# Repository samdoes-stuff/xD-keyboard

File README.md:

# xD-keyboard
xD keyboard is nRF52 based wireless mechanical keyboard equipped with Gateron KS-33 low profile key switches. 

# PCB 

Generated with KLEPCBGEN. Designed with both Kicad & Easyeda PRO.

# Case & Plate 

Generated with Swillkb & Keebio. Designed with Fusion 360. Chopped with Bamboo lab Studio.

Counter sink screw holes

# Bootloader & Firmware

Bootloader generated from Adafruit_nRF52_Bootloader & Firmware made with ZMK with Custom Board.
- ZMK Ultra-Low-Power Mode
- Deep sleep between keypresses
- BLE connection optimization
- Soft-off / idle timeout
- ZMK USB HID (wired mode)

#BOM 

Refer to BOM.csv

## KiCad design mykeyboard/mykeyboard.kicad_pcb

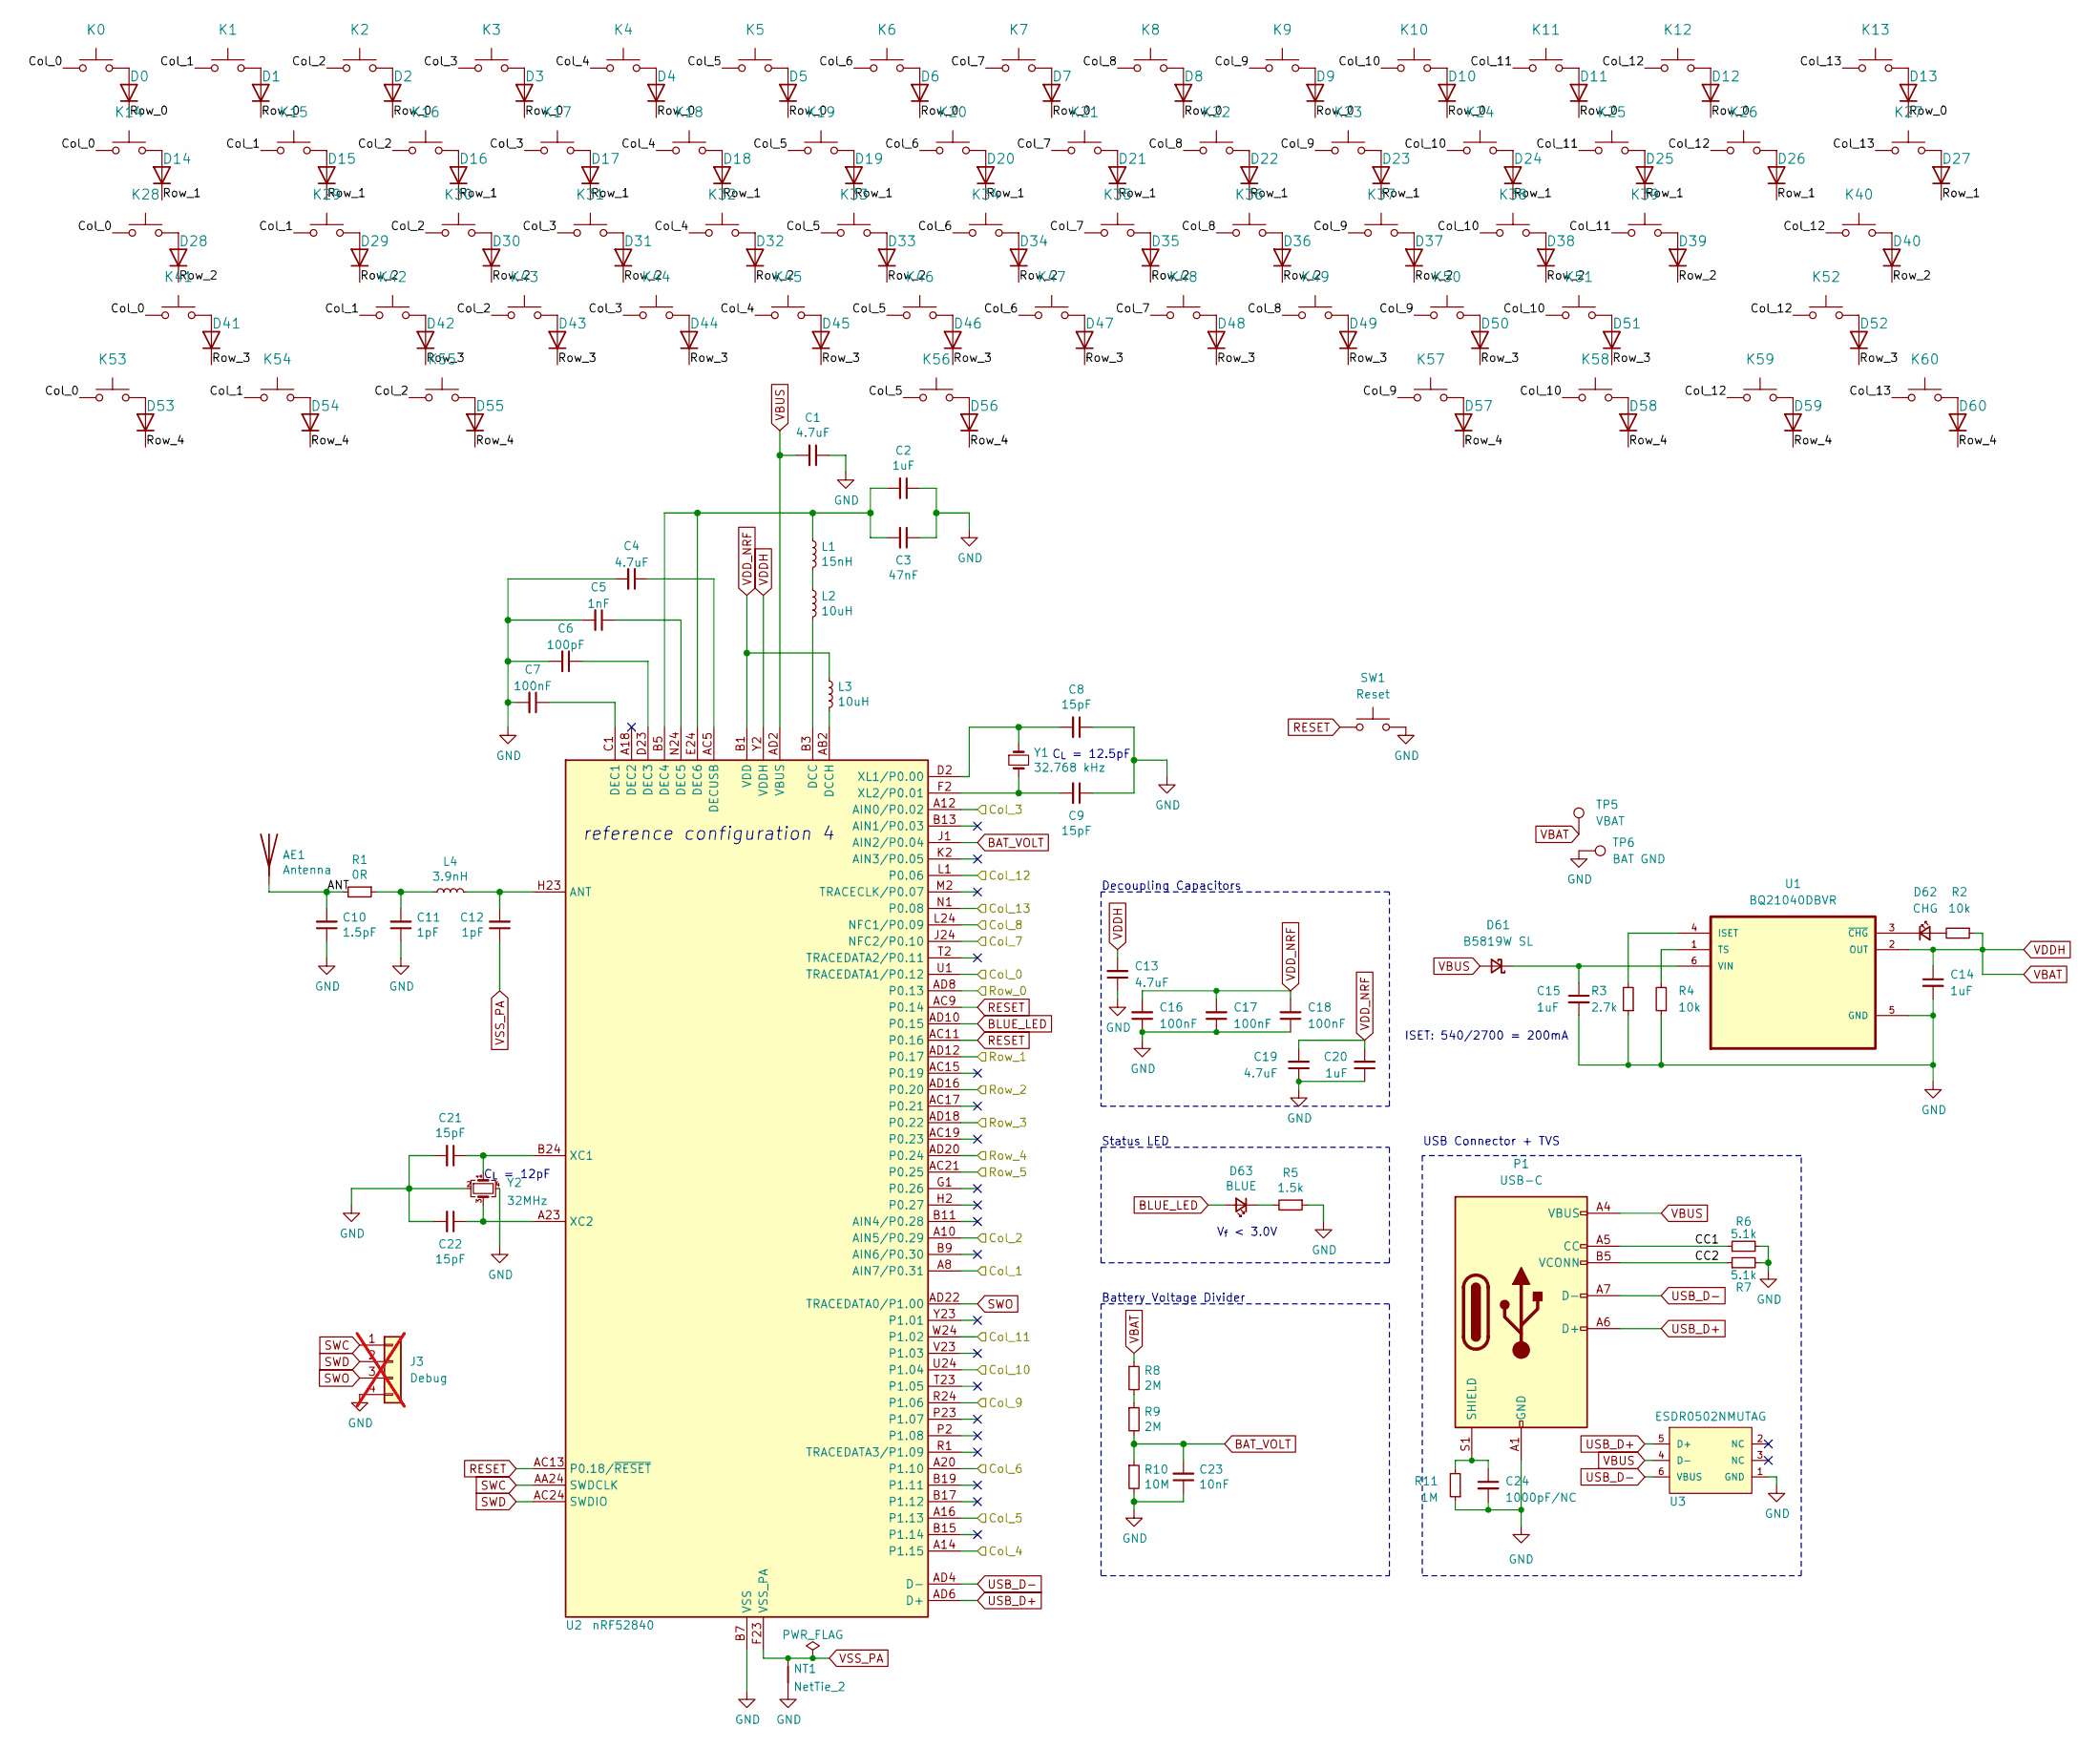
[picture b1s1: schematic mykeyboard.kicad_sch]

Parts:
AE1: Antenna; 2.4GHz-meander-antenna-v2
C1, C4, C13, C19: 4.7uF; C_0402_1005Metric; Manufacturer Part CL05A475KP5NRNC; LCSC C23733
C2, C14, C15, C20: 1uF; C_0402_1005Metric; Manufacturer Part CL05A105KO5NNNC; LCSC C52923
C3: 47nF; C_0402_1005Metric; Manufacturer Part CL05B473KO5NNNC; LCSC C272875
C5: 1nF; C_0402_1005Metric; Manufacturer Part CL05B102KB5NNNC; LCSC C1523
C6: 100pF; C_0402_1005Metric; Manufacturer Part CL05C101JB5NNNC; LCSC C1546
C7, C16, C17, C18: 100nF; C_0402_1005Metric; Manufacturer Part CL05B104KA5NNNC; LCSC C307331
C8, C9, C21, C22: 15pF; C_0402_1005Metric; Manufacturer Part CL05C150JB51PNC; LCSC C1548
C10: 1.5pF; C_0402_1005Metric; Manufacturer Part CL05C1R5CB5NNNC; LCSC C1552
C11, C12: 1pF; C_0402_1005Metric; Manufacturer Part CL05C010CB5NNNC; LCSC C1550
C23: 10nF; C_0402_1005Metric; Manufacturer Part CL05B103KB5NNNC; LCSC C15195
C24: 1000pF/NC; C_0402_1005Metric
D0, D1, D2, D3, D4, D5, D6, D7, D8, D9, D10, D11, D12, D13, D14, D15, D16, D17, D18, D19, D20, D21, D22, D23, D24, D25, D26, D27, D28, D29, D30, D31, D32, D33, D34, D35, D36, D37, D38, D39, D40, D41, D42, D43, D44, D45, D46, D47, D48, D49, D50, D51, D52, D53, D54, D55, D56, D57, D58, D59, D60: D; D_SOD-523
D61: B5819W SL; D_SOD-323; Manufacturer Part PMEG4010CEJ; LCSC C8598
D62: CHG; LED_0603_1608Metric; Manufacturer Part 19-217/S2C-AQ1R1B/3T; LCSC C72038
D63: BLUE; LED_0603_1608Metric; Manufacturer Part 19-217/BHC-ZL1M2RY/3T; LCSC C2290
J3: Debug; PinHeader_1x04_P2.54mm_Vertical; not fitted
K0: ~~,`; Gateron-KS33-Hotswap-1U
K1: !,1; Gateron-KS33-Hotswap-1U
K2: @,2; Gateron-KS33-Hotswap-1U
K3: #,3; Gateron-KS33-Hotswap-1U
K4: $,4; Gateron-KS33-Hotswap-1U
K5: %,5; Gateron-KS33-Hotswap-1U
K6: ^,6; Gateron-KS33-Hotswap-1U
K7: &,7; Gateron-KS33-Hotswap-1U
K8: *,8; Gateron-KS33-Hotswap-1U
K9: (,9; Gateron-KS33-Hotswap-1U
K10: ),0; Gateron-KS33-Hotswap-1U
K11: _,-; Gateron-KS33-Hotswap-1U
K12: +,=; Gateron-KS33-Hotswap-1U
K13: Backspace; Gateron-KS33-Hotswap-2U
K14: Tab; Gateron-KS33-Hotswap-1.5U
K15: Q; Gateron-KS33-Hotswap-1U
K16: W; Gateron-KS33-Hotswap-1U
K17: E; Gateron-KS33-Hotswap-1U
K18: R; Gateron-KS33-Hotswap-1U
K19: T; Gateron-KS33-Hotswap-1U
K20: Y; Gateron-KS33-Hotswap-1U
K21: U; Gateron-KS33-Hotswap-1U
K22: I; Gateron-KS33-Hotswap-1U
K23: O; Gateron-KS33-Hotswap-1U
K24: P; Gateron-KS33-Hotswap-1U
K25: {,[; Gateron-KS33-Hotswap-1U
K26: },]; Gateron-KS33-Hotswap-1U
K27: |,\; Gateron-KS33-Hotswap-1.5U
K28: Caps Lock; Gateron-KS33-Hotswap-1.75U
K29: A; Gateron-KS33-Hotswap-1U
K30: S; Gateron-KS33-Hotswap-1U
K31: D; Gateron-KS33-Hotswap-1U
K32: F; Gateron-KS33-Hotswap-1U
K33: G; Gateron-KS33-Hotswap-1U
K34: H; Gateron-KS33-Hotswap-1U
K35: J; Gateron-KS33-Hotswap-1U
K36: K; Gateron-KS33-Hotswap-1U
K37: L; Gateron-KS33-Hotswap-1U
K38: :,;; Gateron-KS33-Hotswap-1U
K39: ",'; Gateron-KS33-Hotswap-1U
K40: Enter; Gateron-KS33-Hotswap-2.25U
K41: Shift; Gateron-KS33-Hotswap-2.25U
K42: Z; Gateron-KS33-Hotswap-1U
K43: X; Gateron-KS33-Hotswap-1U
K44: C; Gateron-KS33-Hotswap-1U
K45: V; Gateron-KS33-Hotswap-1U
K46: B; Gateron-KS33-Hotswap-1U
K47: N; Gateron-KS33-Hotswap-1U
K48: M; Gateron-KS33-Hotswap-1U
K49: <,,; Gateron-KS33-Hotswap-1U
K50: >,.; Gateron-KS33-Hotswap-1U
K51: ?,/; Gateron-KS33-Hotswap-1U
K52: Shift; Gateron-KS33-Hotswap-2.75U
K53, K60: Ctrl; Gateron-KS33-Hotswap-1.25U
K54, K58: Win; Gateron-KS33-Hotswap-1.25U
K55, K57: Alt; Gateron-KS33-Hotswap-1.25U
K56: Blank; Gateron-KS33-Hotswap-6.25U
K59: Menu; Gateron-KS33-Hotswap-1.25U
L1: 15nH; L_0402_1005Metric; Manufacturer Part MLG1005S15NJT000; LCSC C27143
L2, L3: 10uH; L_0603_1608Metric; Manufacturer Part MLF1608E100KTD00; LCSC C285968
L4: 3.9nH; L_0402_1005Metric; Manufacturer Part MLG1005S3N9BT000; LCSC C14033
NT1: NetTie_2; net-tie-2-tiny
P1: USB-C; USB_C_Receptacle_HRO_TYPE-C-31-M-12; LCSC C165948
R1: 0R; R_0402_1005Metric; Manufacturer Part RC0402FR-070RL; LCSC C17168
R2, R4: 10k; R_0402_1005Metric; Manufacturer Part RC0402FR-0710KL; LCSC C25744
R3: 2.7k; R_0603_1608Metric; Manufacturer Part RC0402FR-0710KL; LCSC C13167
R5: 1.5k; R_0402_1005Metric; Manufacturer Part RC0402FR-071K5L; LCSC C25867
R6, R7: 5.1k; R_0402_1005Metric; Manufacturer Part RC0402FR-075K1L; LCSC C25905
R8, R9: 2M; R_0603_1608Metric; Manufacturer Part RC0402FR-072ML; LCSC C22976
R10: 10M; R_0402_1005Metric; Manufacturer Part RC0402FR-0710ML; LCSC C26082
R11: 1M; R_0402_1005Metric; LCSC C26083
SW1: Reset; SW_Push_1P1T_XKB_TS-1187A; LCSC C318884
TP5: VBAT; TestPoint_Pad_2.5x2.5mm
TP6: BAT GND; TestPoint_Pad_2.5x2.5mm
U1: BQ21040DBVR; SOT95P280X145-6N; LCSC C202311
U2: nRF52840; Nordic_AQFN-73-1EP_7x7mm_P0.5mm; Manufacturer Part NRF52840-QIAA-R; LCSC C190794
U3: ESDR0502NMUTAG; UDFN-6_1.2x1.0mm_P0.4mm; Manufacturer Part ESDR0502NMUTBG; LCSC C327480
Y1: 32.768 kHz; Crystal_SMD_2012-2Pin_2.0x1.2mm; Manufacturer Part SC20S-12.5PF20PPM; LCSC C99009
Y2: 32MHz; Crystal_SMD_2016-4Pin_2.0x1.6mm; Manufacturer Part Q22FA1280001800; LCSC C2965584

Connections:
/ANT: AE1.1 (A), C10.2, R1.2
/CC1: P1.A5 (CC), R6.1
/CC2: P1.B5 (VCONN), R7.1
/Col_0: K0.1, K14.1, K28.1, K41.1, K53.1, U2.U1 (TRACEDATA1/P0.12)
/Col_1: K1.1, K15.1, K29.1, K42.1, K54.1, U2.A8 (AIN7/P0.31)
/Col_2: K2.1, K16.1, K30.1, K43.1, K55.1, U2.A10 (AIN5/P0.29)
/Col_3: K3.1, K17.1, K31.1, K44.1, U2.A12 (AIN0/P0.02)
/Col_4: K4.1, K18.1, K32.1, K45.1, U2.A14 (P1.15)
/Col_5: K5.1, K19.1, K33.1, K46.1, K56.1, U2.A16 (P1.13)
/Col_6: K6.1, K20.1, K34.1, K47.1, U2.A20 (P1.10)
/Col_7: K7.1, K21.1, K35.1, K48.1, U2.J24 (NFC2/P0.10)
/Col_8: K8.1, K22.1, K36.1, K49.1, U2.L24 (NFC1/P0.09)
/Col_9: K9.1, K23.1, K37.1, K50.1, K57.1, U2.R24 (P1.06)
/Col_10: K10.1, K24.1, K38.1, K51.1, K58.1, U2.U24 (P1.04)
/Col_11: K11.1, K25.1, K39.1, U2.W24 (P1.02)
/Col_12: K12.1, K26.1, K40.1, K52.1, K59.1, U2.L1 (P0.06)
/Col_13: K13.1, K27.1, K60.1, U2.N1 (P0.08)
/Row_0: D0.1 (K), D1.1 (K), D2.1 (K), D3.1 (K), D4.1 (K), D5.1 (K), D6.1 (K), D7.1 (K), D8.1 (K), D9.1 (K), D10.1 (K), D11.1 (K), D12.1 (K), D13.1 (K), U2.AD8 (P0.13)
/Row_1: D14.1 (K), D15.1 (K), D16.1 (K), D17.1 (K), D18.1 (K), D19.1 (K), D20.1 (K), D21.1 (K), D22.1 (K), D23.1 (K), D24.1 (K), D25.1 (K), D26.1 (K), D27.1 (K), U2.AD12 (P0.17)
/Row_2: D28.1 (K), D29.1 (K), D30.1 (K), D31.1 (K), D32.1 (K), D33.1 (K), D34.1 (K), D35.1 (K), D36.1 (K), D37.1 (K), D38.1 (K), D39.1 (K), D40.1 (K), U2.AD16 (P0.20)
/Row_3: D41.1 (K), D42.1 (K), D43.1 (K), D44.1 (K), D45.1 (K), D46.1 (K), D47.1 (K), D48.1 (K), D49.1 (K), D50.1 (K), D51.1 (K), D52.1 (K), U2.AD18 (P0.22)
/Row_4: D53.1 (K), D54.1 (K), D55.1 (K), D56.1 (K), D57.1 (K), D58.1 (K), D59.1 (K), D60.1 (K), U2.AD20 (P0.24)
BAT_VOLT: C23.2, R9.2, R10.1, U2.J1 (AIN2/P0.04)
BLUE_LED: D63.2 (A), U2.AD10 (P0.15)
unnamed: C11.2, L4.1, R1.1
unnamed: D0.2 (A), K0.2
unnamed: D1.2 (A), K1.2
unnamed: D2.2 (A), K2.2
unnamed: D3.2 (A), K3.2
unnamed: D4.2 (A), K4.2
unnamed: D5.2 (A), K5.2
unnamed: D6.2 (A), K6.2
unnamed: D7.2 (A), K7.2
unnamed: D8.2 (A), K8.2
unnamed: D9.2 (A), K9.2
unnamed: D10.2 (A), K10.2
unnamed: D11.2 (A), K11.2
unnamed: D12.2 (A), K12.2
unnamed: D13.2 (A), K13.2
unnamed: D14.2 (A), K14.2
unnamed: D15.2 (A), K15.2
unnamed: D16.2 (A), K16.2
unnamed: D17.2 (A), K17.2
unnamed: D18.2 (A), K18.2
unnamed: D19.2 (A), K19.2
unnamed: D20.2 (A), K20.2
unnamed: D21.2 (A), K21.2
unnamed: D22.2 (A), K22.2
unnamed: D23.2 (A), K23.2
unnamed: D24.2 (A), K24.2
unnamed: D25.2 (A), K25.2
unnamed: D26.2 (A), K26.2
unnamed: D27.2 (A), K27.2
unnamed: D28.2 (A), K28.2
unnamed: D29.2 (A), K29.2
unnamed: D30.2 (A), K30.2
unnamed: D31.2 (A), K31.2
unnamed: D32.2 (A), K32.2
unnamed: D33.2 (A), K33.2
unnamed: D34.2 (A), K34.2
unnamed: D35.2 (A), K35.2
unnamed: D36.2 (A), K36.2
unnamed: D37.2 (A), K37.2
unnamed: D38.2 (A), K38.2
unnamed: D39.2 (A), K39.2
unnamed: D40.2 (A), K40.2
unnamed: D41.2 (A), K41.2
unnamed: D42.2 (A), K42.2
unnamed: D43.2 (A), K43.2
unnamed: D44.2 (A), K44.2
unnamed: D45.2 (A), K45.2
unnamed: D46.2 (A), K46.2
unnamed: D47.2 (A), K47.2
unnamed: D48.2 (A), K48.2
unnamed: D49.2 (A), K49.2
unnamed: D50.2 (A), K50.2
unnamed: D51.2 (A), K51.2
unnamed: D52.2 (A), K52.2
unnamed: D53.2 (A), K53.2
unnamed: D54.2 (A), K54.2
unnamed: D55.2 (A), K55.2
unnamed: D56.2 (A), K56.2
unnamed: D57.2 (A), K57.2
unnamed: D58.2 (A), K58.2
unnamed: D59.2 (A), K59.2
unnamed: D60.2 (A), K60.2
unnamed: C15.1, D61.1 (K), U1.6 (VIN)
unnamed: D62.2 (A), R2.2
unnamed: D62.1 (K), U1.3 (~CHG)
unnamed: D63.1 (K), R5.2
unnamed: L1.2, L2.1
unnamed: C24.1, P1.S1 (SHIELD), R11.2
unnamed: R8.2, R9.1
unnamed: R3.2, U1.4 (ISET)
unnamed: R4.2, U1.1 (TS)
unnamed: C12.2, L4.2, U2.H23 (ANT)
unnamed: L2.2, U2.B3 (DCC)
unnamed: L3.2, U2.AB2 (DCCH)
unnamed: C7.1, U2.C1 (DEC1)
unnamed: C6.1, U2.D23 (DEC3)
unnamed: C2.2, C3.2, L1.1, U2.B5 (DEC4), U2.E24 (DEC6)
unnamed: C5.1, U2.N24 (DEC5)
unnamed: C4.1, U2.AC5 (DECUSB)
unnamed: C21.1, U2.B24 (XC1), Y2.1
unnamed: C22.1, U2.A23 (XC2), Y2.3
unnamed: C8.2, U2.D2 (XL1/P0.00), Y1.1
unnamed: C9.2, U2.F2 (XL2/P0.01), Y1.2
RESET: SW1.1, U2.AC9 (P0.14), U2.AC11 (P0.16), U2.AC13 (P0.18/~RESET)
USB_D+: P1.A6 (D+), P1.B6 (D+), U2.AD6 (D+), U3.5 (D+)
USB_D-: P1.A7 (D-), P1.B7 (D-), U2.AD4 (D-), U3.6 (VBUS)
VBAT: C13.2, C14.1, R2.1, R8.1, TP5.1, U1.2 (OUT), U2.Y2 (VDDH)
VBUS: C1.2, D61.2 (A), P1.A4 (VBUS), P1.A9 (VBUS), P1.B4 (VBUS), P1.B9 (VBUS), U2.AD2 (VBUS), U3.4 (D-)
VDD_NRF: C16.2, C17.2, C18.2, C19.2, C20.2, L3.1, U2.A22 (VDD), U2.AD14 (VDD), U2.AD23 (VDD), U2.B1 (VDD), U2.W1 (VDD)
VSS_PA: C12.1, NT1.1, U2.F23 (VSS_PA)

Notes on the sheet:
C_{L} = 12pF
Battery Voltage Divider
V_{f} < 3.0V
Decoupling Capacitors
ISET: 540/2700 = 200mA
reference configuration 4
Status LED
USB Connector + TVS
C_{L} = 12.5pF

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
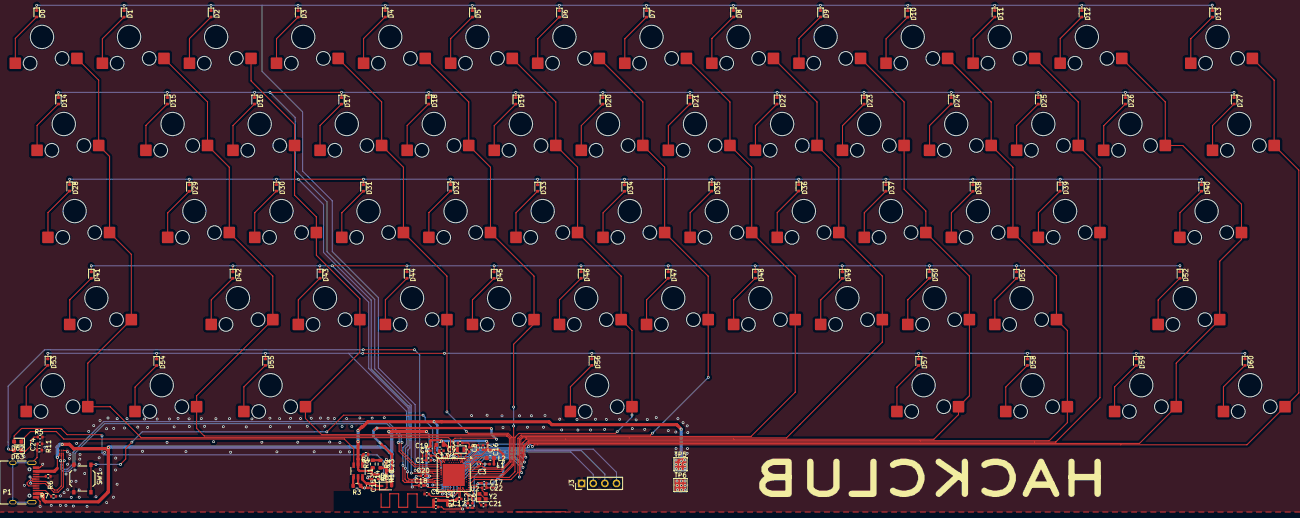
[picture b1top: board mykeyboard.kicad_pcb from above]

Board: 2 copper layers, 176 parts (0 on the bottom side), 118 nets.

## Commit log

2025-12-20 Create 0
2025-12-21 Create Adafruit_nRF52_Bootloader
2025-12-24 Create Cherry_MX_ULP
2026-01-06 PUSH MY BOY
2026-01-07 Plate Me
2026-01-08 Thas how cooking work
2026-01-08 Found cheaper things
2026-01-09 ITSY CHANGE
2026-01-09 Little space update
2026-01-09 Stabilizer Cost add
2026-01-09 Enhance README with additional project details
    Expanded the README with detailed sections on PCB, case, bootloader, and BOM.
